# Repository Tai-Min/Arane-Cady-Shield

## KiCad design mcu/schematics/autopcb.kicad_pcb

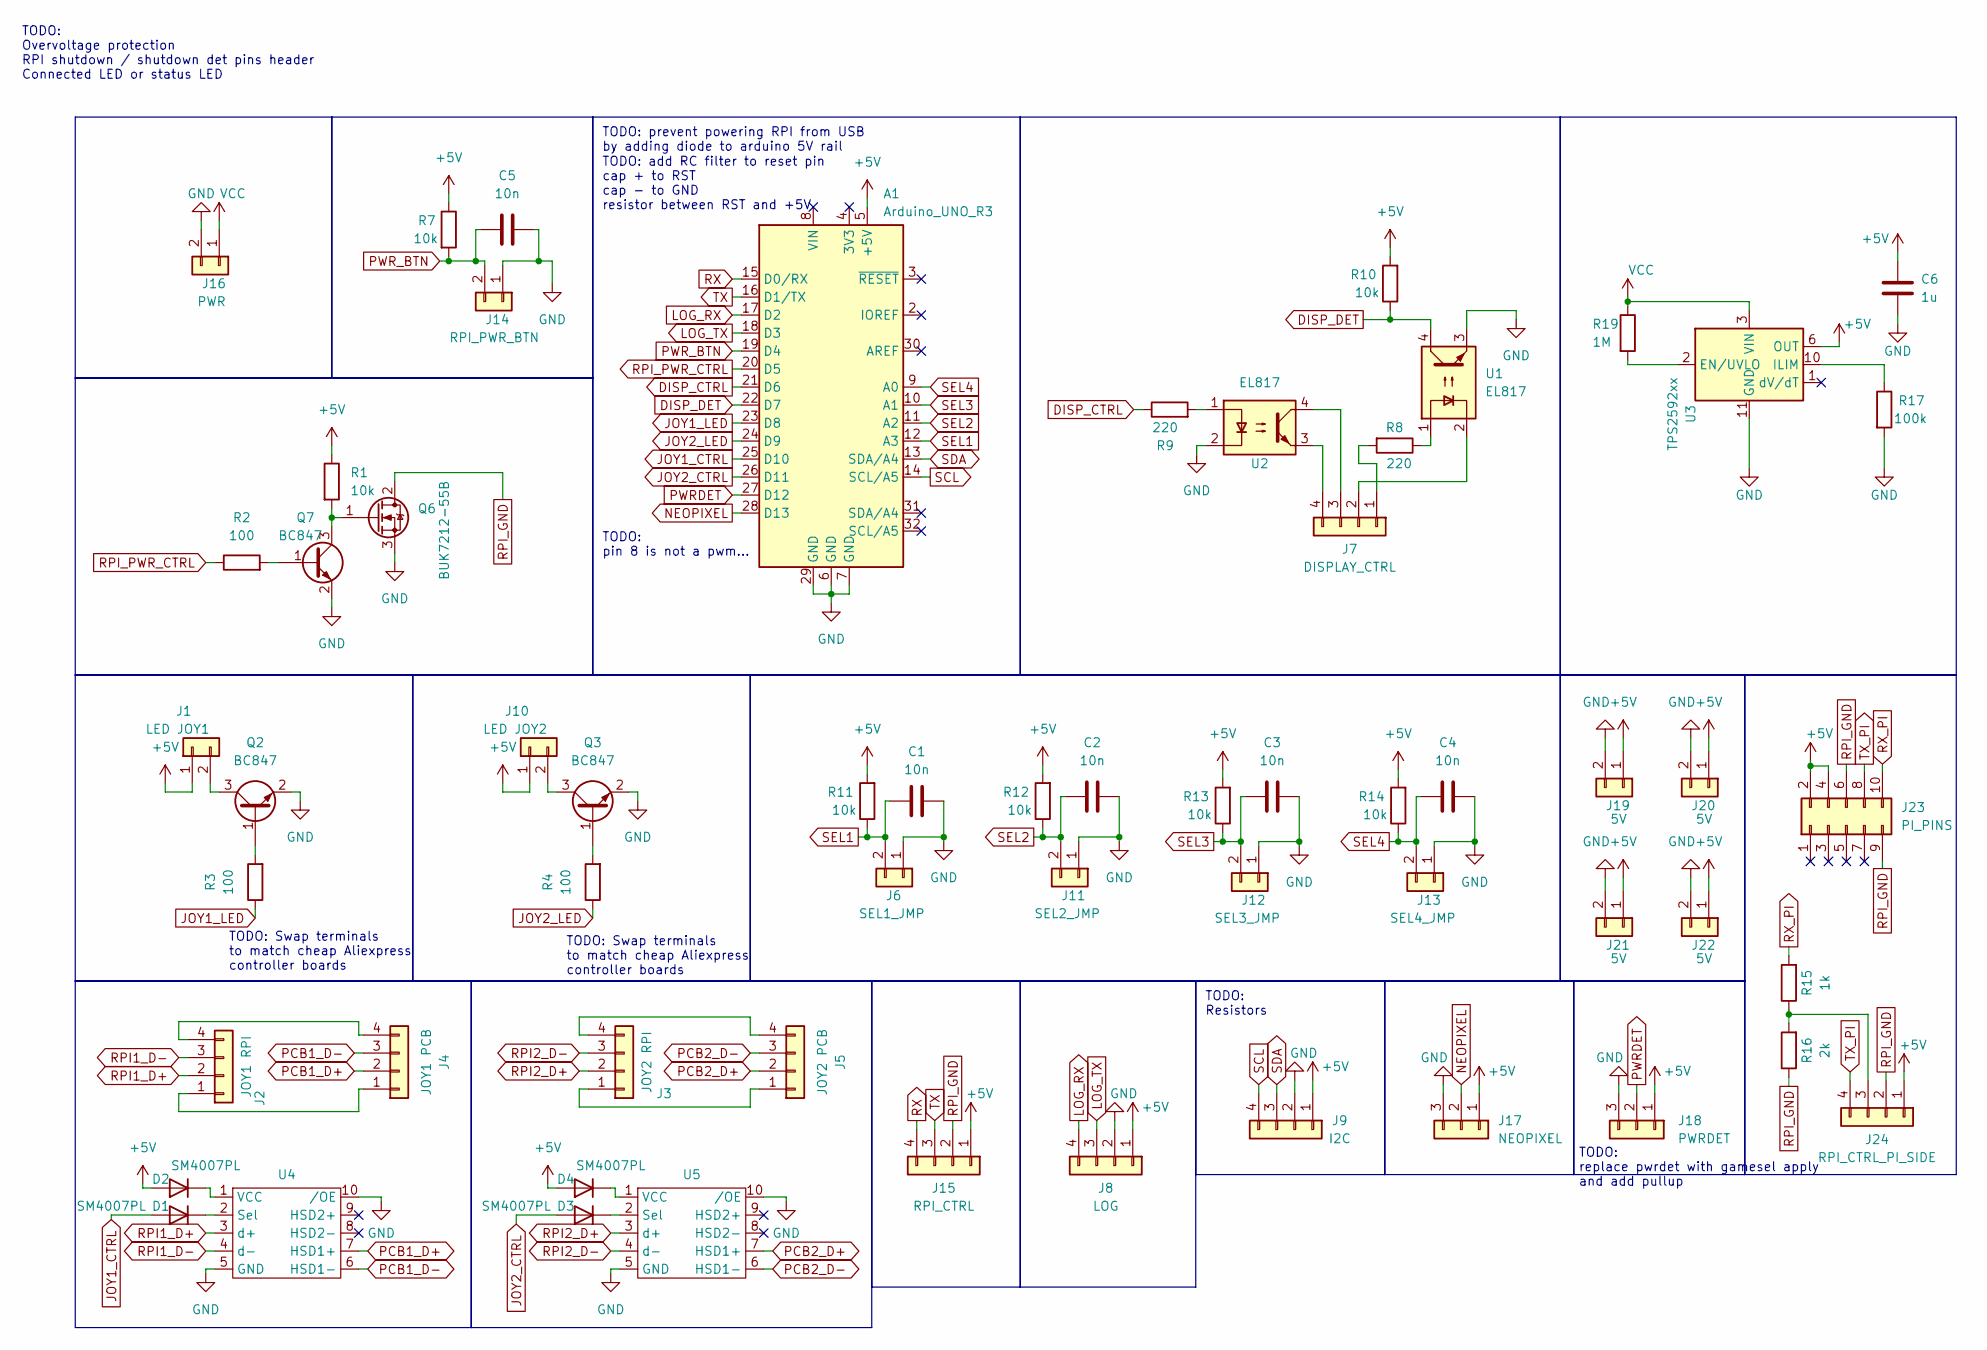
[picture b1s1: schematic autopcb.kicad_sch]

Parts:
A1: Arduino_UNO_R3
C1, C2, C3, C4, C5: 10n; C_1206_3216Metric
C6: 1u; C_1206_3216Metric
D1, D2, D3, D4: SM4007PL; D_SOD-123F
J1: LED JOY1; JST_XH_B2B-XH-A_1x02_P2.50mm_Vertical
J2: JOY1 RPI; JST_XH_B4B-XH-A_1x04_P2.50mm_Vertical
J3: JOY2 RPI; JST_XH_B4B-XH-A_1x04_P2.50mm_Vertical
J4: JOY1 PCB; JST_XH_B4B-XH-A_1x04_P2.50mm_Vertical
J5: JOY2 PCB; JST_XH_B4B-XH-A_1x04_P2.50mm_Vertical
J6: SEL1_JMP; PinHeader_1x02_P2.54mm_Vertical
J7: DISPLAY_CTRL; JST_XH_B4B-XH-A_1x04_P2.50mm_Vertical
J8: LOG; JST_XH_B4B-XH-A_1x04_P2.50mm_Vertical
J9: I2C; JST_XH_B4B-XH-A_1x04_P2.50mm_Vertical
J10: LED JOY2; JST_XH_B2B-XH-A_1x02_P2.50mm_Vertical
J11: SEL2_JMP; PinHeader_1x02_P2.54mm_Vertical
J12: SEL3_JMP; PinHeader_1x02_P2.54mm_Vertical
J13: SEL4_JMP; PinHeader_1x02_P2.54mm_Vertical
J14: RPI_PWR_BTN; JST_XH_B2B-XH-A_1x02_P2.50mm_Vertical
J15: RPI_CTRL; JST_XH_B4B-XH-A_1x04_P2.50mm_Vertical
J16: PWR; JST_XH_B2B-XH-A_1x02_P2.50mm_Vertical
J17: NEOPIXEL; JST_XH_B3B-XH-A_1x03_P2.50mm_Vertical
J18: PWRDET; JST_XH_B3B-XH-A_1x03_P2.50mm_Vertical
J19, J20, J21, J22: 5V; JST_XH_B2B-XH-A_1x02_P2.50mm_Vertical
J23: PI_PINS; PinSocket_2x05_P2.54mm_Vertical
J24: RPI_CTRL_PI_SIDE; JST_XH_B4B-XH-A_1x04_P2.50mm_Vertical
Q2, Q3, Q7: BC847; SOT-23
Q6: BUK7212-55B; TO-252-2
R1, R7, R10, R11, R12, R13, R14: 10k; R_1206_3216Metric
R2, R3, R4: 100; R_0805_2012Metric
R8, R9: 220; R_1206_3216Metric
R15: 1k; R_1206_3216Metric
R16: 2k; R_1206_3216Metric
R17: 100k; R_0805_2012Metric
R19: 1M; R_0805_2012Metric
U1, U2: EL817; DIP-4_W7.62mm_SMDSocket_SmallPads
U3: TPS2592xx; VSON-10-1EP_3x3mm_P0.5mm_EP1.65x2.4mm_ThermalVias
U4, U5: MSOP-10-1EP_3x3mm_P0.5mm_EP1.68x1.88mm

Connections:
+5V: A1.5 (+5V), C6.2, D2.2 (A), D4.2 (A), J1.1, J8.1, J9.1, J10.1, J15.1, J17.1, J18.1, J19.1, J20.1, J21.1, J22.1, J23.2, J23.4, J24.1, R1.1, R7.1, R10.2, R11.2, R12.2, R13.2, R14.2, U3.6 (OUT), U3.7 (OUT), U3.8 (OUT)
DISP_CTRL: A1.21 (D6), R9.1
DISP_DET: A1.22 (D7), R10.1, U1.4
GND: A1.6 (GND), A1.7 (GND), A1.29 (GND), C1.2, C2.2, C3.2, C4.2, C5.2, C6.1, J6.1, J8.2, J9.2, J11.1, J12.1, J13.1, J14.1, J16.2, J17.3, J18.3, J19.2, J20.2, J21.2, J22.2, Q2.2 (E), Q3.2 (E), Q6.3 (S), Q7.2 (E), R17.2, U1.3, U2.2, U3.11 (GND), U4.5 (GND), U4.10 (/OE), U5.5 (GND), U5.10 (/OE)
JOY1_CTRL: A1.25 (D10), D1.2 (A)
JOY1_LED: A1.23 (D8), R3.1
JOY2_CTRL: A1.26 (D11), D3.2 (A)
JOY2_LED: A1.24 (D9), R4.1
LOG_RX: A1.17 (D2), J8.4
LOG_TX: A1.18 (D3), J8.3
NEOPIXEL: A1.28 (D13), J17.2
unnamed: D1.1 (K), U4.2 (Sel)
unnamed: D2.1 (K), U4.1 (VCC)
unnamed: D3.1 (K), U5.2 (Sel)
unnamed: D4.1 (K), U5.1 (VCC)
unnamed: J1.2, Q2.3 (C)
unnamed: J2.1, J4.1
unnamed: J2.4, J4.4
unnamed: J3.1, J5.1
unnamed: J3.4, J5.4
unnamed: J7.1, R8.2
unnamed: J7.2, U1.2
unnamed: J7.3, U2.4
unnamed: J7.4, U2.3
unnamed: J10.2, Q3.3 (C)
unnamed: J24.3, R15.1, R16.2
unnamed: Q2.1 (B), R3.2
unnamed: Q3.1 (B), R4.2
unnamed: Q6.1 (G), Q7.3 (C), R1.2
unnamed: Q7.1 (B), R2.2
unnamed: R8.1, U1.1
unnamed: R9.2, U2.1
unnamed: R19.2, U3.2 (EN/UVLO)
unnamed: R17.1, U3.10 (ILIM)
PCB1_D+: J4.2, U4.7 (HSD1+)
PCB1_D-: J4.3, U4.6 (HSD1-)
PCB2_D+: J5.2, U5.7 (HSD1+)
PCB2_D-: J5.3, U5.6 (HSD1-)
PWRDET: A1.27 (D12), J18.2
PWR_BTN: A1.19 (D4), C5.1, J14.2, R7.2
RPI1_D+: J2.2, U4.3 (d+)
RPI1_D-: J2.3, U4.4 (d-)
RPI2_D+: J3.2, U5.3 (d+)
RPI2_D-: J3.3, U5.4 (d-)
RPI_GND: J15.2, J23.6, J23.9, J24.2, Q6.2 (D), R16.1
RPI_PWR_CTRL: A1.20 (D5), R2.1
RX: A1.15 (D0/RX), J15.4
RX_PI: J23.10, R15.2
SCL: A1.14 (SCL/A5), J9.4
SDA: A1.13 (SDA/A4), J9.3
SEL1: A1.12 (A3), C1.1, J6.2, R11.1
SEL2: A1.11 (A2), C2.1, J11.2, R12.1
SEL3: A1.10 (A1), C3.1, J12.2, R13.1
SEL4: A1.9 (A0), C4.1, J13.2, R14.1
TX: A1.16 (D1/TX), J15.3
TX_PI: J23.8, J24.4
VCC: J16.1, R19.1, U3.3 (VIN), U3.4 (VIN), U3.5 (VIN)

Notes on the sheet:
TODO: add RC filter to reset pin cap + to RST cap - to GND resistor between RST and +5V
TODO: replace pwrdet with gamesel apply and add pullup
TODO: Overvoltage protection RPI shutdown / shutdown det pins header Connected LED or status LED
TODO: prevent powering RPI from USB by adding diode to arduino 5V rail
TODO: pin 8 is not a pwm...
TODO: Swap terminals to match cheap Aliexpress controller boards
TODO: Resistors

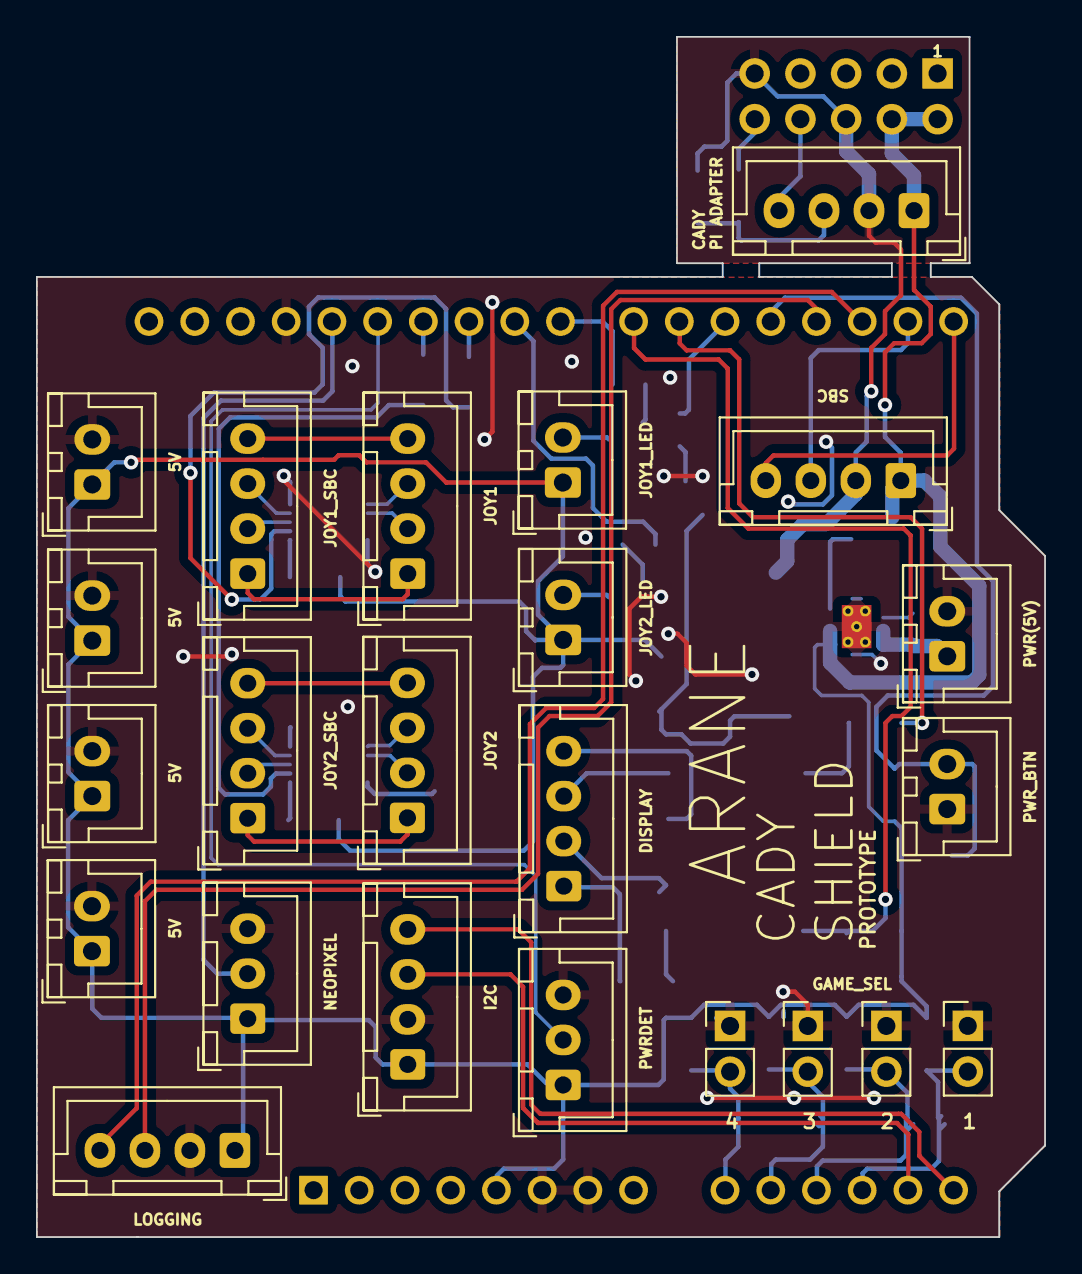
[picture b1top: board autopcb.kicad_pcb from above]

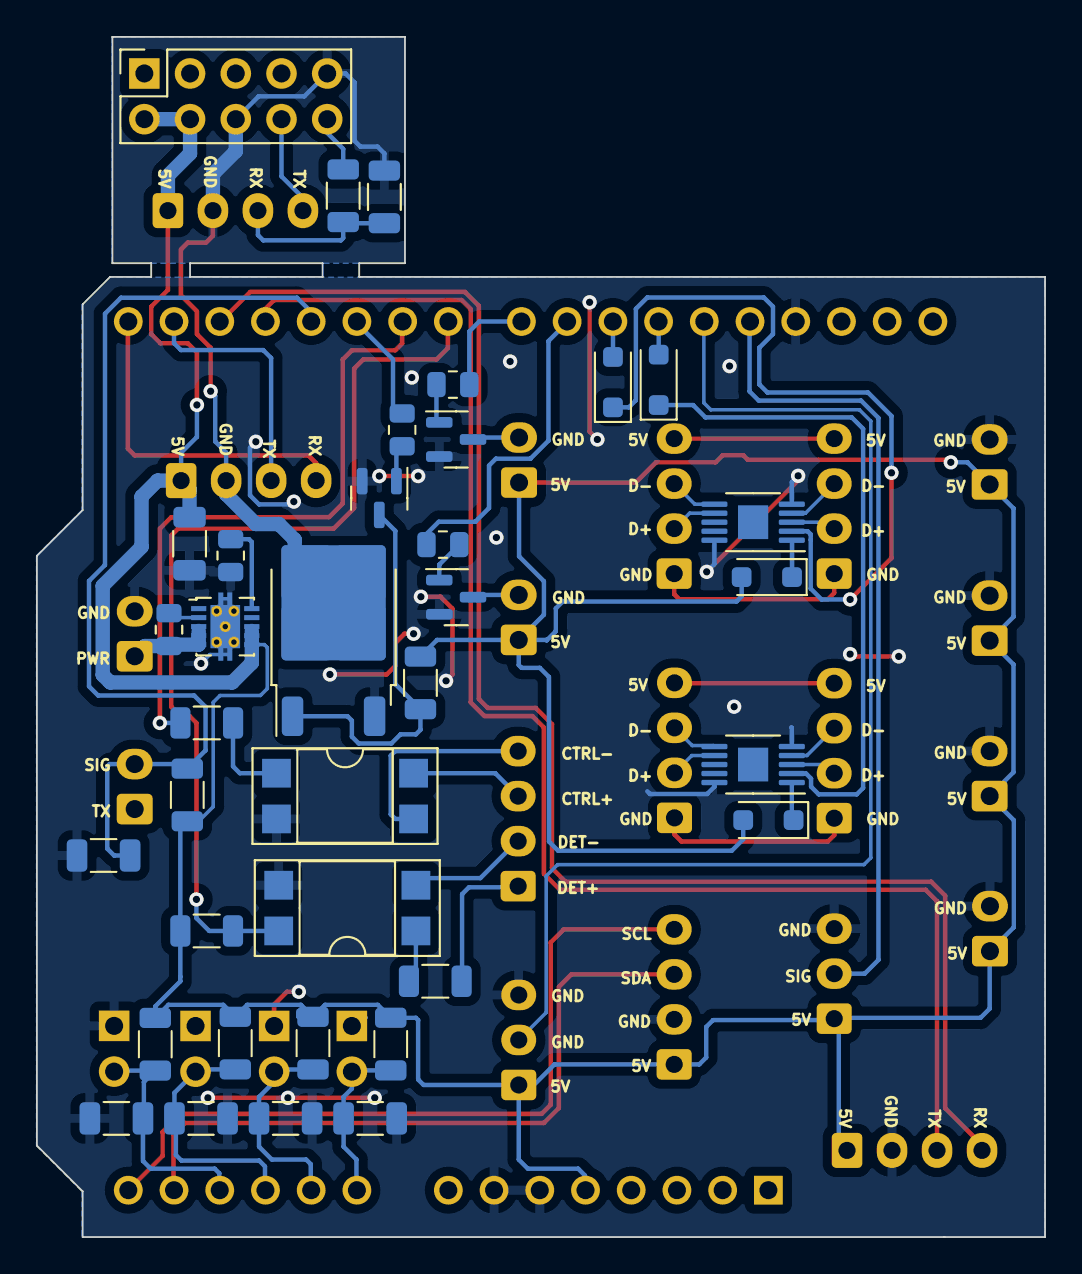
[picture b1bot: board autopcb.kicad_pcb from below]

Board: 2 copper layers, 56.0 x 66.7 mm, 60 parts (37 on the bottom side), 57 nets.

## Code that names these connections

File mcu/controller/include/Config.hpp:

#pragma once
#include <Arduino.h>

#define GAME_SELECTOR_ENCODER

namespace Config
{
    namespace Main
    {
        constexpr long LOG_BAUD = 9600;

        namespace GPIO
        {
            constexpr uint8_t LOG_SERIAL_RX = 2;
            constexpr uint8_t LOG_SERIAL_TX = 3;
        }
    }

    namespace AppTask
    {
        constexpr unsigned long BOOT_TIMEOUT_DURATION = 240000; // If boot time exceeds this time the app goes into error state.
        constexpr unsigned long SHUTDOWN_DURATION = 60000;      // How long to wait for shutdown to turn off SBC.
    }

    namespace DisplayTask
    {
        constexpr bool INVERT_DET = true;   // If true then if diode on display is lit then digital low is delivered to MCU.
        constexpr bool INVERT_CTRL = false; // If true then digital low state is considered a button press on the display.

        constexpr uint16_t LOOP_DELAY = 100;              // Delay between display task loop iterations.
        constexpr uint16_t DISABLE_CHECK_DURATION = 2000; // For how long to check whether display is ON or OFF.
        constexpr uint16_t STATE_TRANSITION_DELAY = 2000; // How long to wait for display to change state.

        namespace GPIO
        {
            constexpr uint8_t DISP_DET = 7;
            constexpr uint8_t DISP_CTRL = 6;
        }
    }

    namespace Communication
    {
        constexpr uint8_t SBC_HB_MAX_RETRIES = 10;          // How many retries of SBC heartbeat until MCU decides that it's disconnected.
        constexpr unsigned long SBC_HB_CHECK_PERIOD = 2000; // How frequently check for SBC heartbeat.

        constexpr uint8_t DEVICE_ID = 1; // Slave ID

        constexpr unsigned long SERIAL_BAUD = 19200;
        constexpr unsigned long SERIAL_TIMEOUT = 50;

        namespace Coils // Coils (inputs to MCU)
        {

            constexpr uint8_t Q_SHUTDOWN_FLAG_ADDR = 0; // Info from SBC that it's shutting down.
            constexpr uint8_t Q_DISPLAY_STATE_ADDR = 1;
            constexpr uint8_t Q_JOY1_ENA_FLAG_ADDR = 2;
            constexpr uint8_t Q_JOY2_ENA_FLAG_ADDR = 3;
        }

        namespace Inputs // Inputs (outputs from MCU)
        {
            constexpr uint8_t I_SHUTDOWN_REQ_ADDR = 0; // Request from MCU to shutdown SBC.
        }

        namespace HoldingRegs // Holding regs (inputs to MCU)
        {
            constexpr uint8_t AQ_SBC_HB_CNTR_ADDR = 0;
            constexpr uint8_t AQ_JOY1_LED_BRIGHTNESS_ADDR = 1;
            constexpr uint8_t AQ_JOY2_LED_BRIGHTNESS_ADDR = 2;
        }
        namespace InputRegs // Input regs (outputs from MCU)
        {
            constexpr uint8_t AI_MCU_HB_CNTR_ADDR = 0;
            constexpr uint8_t AI_MCU_GAMESEL_ADDR = 1;
        }
    }

    namespace LightEffector
    {
        constexpr float BLINKING_RATIO = 0.1;       // Speed of blinking tied to delta time.
        constexpr float FAST_BLINKING_RATIO = 0.75; // Speed of fast blinking tied to delta time.

        namespace GPIO
        {
            constexpr uint8_t JOY1_LED = 8;
            constexpr uint8_t JOY2_LED = 9;
        }
    }

    namespace GameSelector
    {
        constexpr bool APPLY_BTN_LOGIC_INVERTED = true;

#ifdef GAME_SELECTOR_ENCODER
        constexpr bool ENCODER_DIR_INVERTED = true;
#else
        constexpr bool SELECTORS_LOGIC_INVERTED = true;
#endif

        namespace GPIO
        {
            constexpr uint8_t APPLY_BTN = 12;

            constexpr uint8_t SELECTOR_NUM_PINS = 4; // Edit object declaration with more pins if changed!
            constexpr uint8_t SELECTOR_BITS[SELECTOR_NUM_PINS] = {A3, A2, A1, A0};
        }
    }

    namespace SBC
    {
        constexpr bool LOGIC_INVERTED = true;

        namespace GPIO
        {
            constexpr uint8_t RPI_PWR_CTRL = 5;
        }
    }

    namespace Joy
    {
        constexpr bool LOGIC_INVERTED = true;

        namespace GPIO
        {
            constexpr uint8_t JOY1_CTRL = 10;
            constexpr uint8_t JOY2_CTRL = 11;
        }
    }

    namespace PwrButton
    {
        constexpr unsigned long CLICK_TIMEOUT = 500;
        constexpr unsigned long LONG_PRESS_MIN_TIME = 3000;

        constexpr bool LOGIC_INVERTED = true;

        namespace GPIO
        {
            constexpr uint8_t RPI_PWR_BTN = 4;
        }
    }

    namespace PWM
    {
        constexpr uint8_t NUM_MCU_PINS = 13;
    }
}

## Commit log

2024-09-16 Daemon edits
2024-09-18 Bug fixes, add custom libs to project
